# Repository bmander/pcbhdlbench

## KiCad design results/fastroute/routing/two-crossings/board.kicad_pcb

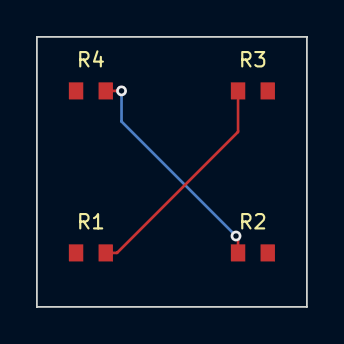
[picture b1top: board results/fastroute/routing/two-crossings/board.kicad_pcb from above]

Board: 2 copper layers, 15.0 x 15.0 mm, 4 parts (0 on the bottom side), 2 nets.

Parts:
R1, R2, R3, R4: R_0603

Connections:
A: R1.2, R3.1
B: R2.1, R4.2

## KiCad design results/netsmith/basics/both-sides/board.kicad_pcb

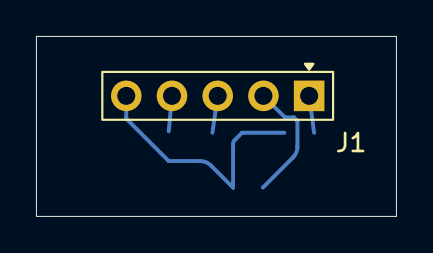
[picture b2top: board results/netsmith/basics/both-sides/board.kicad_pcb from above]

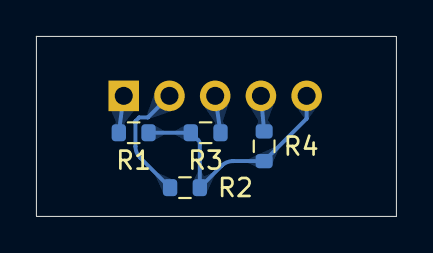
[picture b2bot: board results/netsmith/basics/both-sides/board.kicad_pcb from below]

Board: 2 copper layers, 20.0 x 10.0 mm, 5 parts (4 on the bottom side), 5 nets.

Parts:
J1: Header1x5; PinHeader_pins5_pitch2.54mm_rows1
R1, R2, R3, R4: 10k; R_0603_1608Metric

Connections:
net-j1.p1: J1.1, R1.1
net-j1.p2: J1.2, R2.1
net-j1.p3: J1.3, R3.1
net-j1.p4: J1.4, R4.1
net-j1.p5: J1.5, R1.2, R2.2, R3.2, R4.2

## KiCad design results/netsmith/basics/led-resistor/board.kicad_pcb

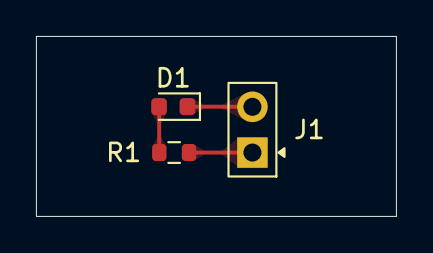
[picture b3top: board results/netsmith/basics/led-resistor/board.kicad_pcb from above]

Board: 2 copper layers, 20.0 x 10.0 mm, 3 parts (0 on the bottom side), 3 nets.

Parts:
D1: KT-0603R; LED_0603_1608Metric
J1: Conn_01x02; PinHeader_1x02_P2.54mm_Vertical
R1: 330; R_0603_1608Metric

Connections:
net-d1.anode: D1.2, R1.2
net-d1.cathode: D1.1, J1.2
net-j1.p1: J1.1, R1.1
